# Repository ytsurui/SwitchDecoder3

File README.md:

# SwitchDecoder3

NMRA DCC規格のアクセサリパケットを受信して、直流二線式のポイント線路を動作させることができるアクセサリデコーダです。

本リポジトリには、基板設計データとファームウェア、動作確認用ファームウェアが含まれています。

## 開発環境

- KiCad 6.0.8
- Microchip Studio Version 7.0.2542

## 主要スペック

  * 組み立て後の基板サイズ: 15.5mm x 8.0mm
  * 推奨最大電圧: 16V
  * 出力電流: 最大2A (ピーク3A)
  * マイコン書き込み端子を用意し、実装後のプログラム書き換えも可能
    <br>UPDI 2pin Interface (GND / UPDI)

## 通常ファームウェア (Firmware)

設定したアクセサリアドレスに応じたDCCパケットを受信すると、ポイント線路を動作させます。

通電開始時にPROG端子に取り付けた配線をどちらかの線路に接触させることで、プログラムモードで起動します。

プログラムモードで起動している間に、同一のアクセサリアドレスに対する操作を連続して3回以上送信することで、設定されているアクセサリアドレスを送信したものに変更することができます。

また、CV値の書き込みにより、通電時間や通電開始までの遅延時間など、細かい動作の調整や、設定のリセットも可能です。

## 動作確認用ファームウェア (Firm_Test)

アクセサリアドレス「1」固定でDCCパケットを受信して動作できる機能と、PROG端子を線路に接触させると約1秒おきにポイント線路の転換動作を行うようにプログラムを作成してあります。

このファームウェアを書き込むことで、SwitchDecoder3基板のDCC入力、PROG端子、モータードライバ回路のすべてをテストすることができます。
  
## 各種ドキュメント

  * [マイコンのピンアサイン](docs/pin.md)
  * [パーツリスト](docs/partslist.md)
  * [CV値一覧](docs/cv_list.md)
  * [AVR Fuse Bitの設定内容](docs/avrfuse.md)

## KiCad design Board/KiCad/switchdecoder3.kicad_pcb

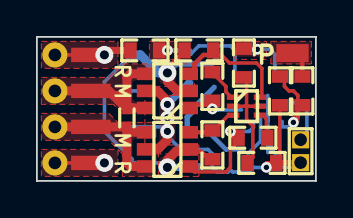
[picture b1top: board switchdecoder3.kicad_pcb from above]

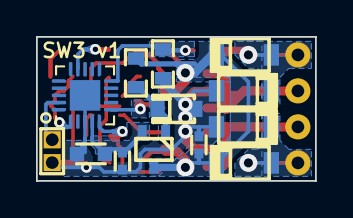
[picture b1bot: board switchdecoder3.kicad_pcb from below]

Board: 2 copper layers, 15.5 x 8.0 mm, 32 parts (13 on the bottom side), 20 nets.

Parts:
C1, C5: 104; C_1005
C3: 226; C_1608
C7: 182; C_1005
D1, D2, D3, D4: SS2040FL; PMDU
D5: UDZV5.1B; UMD2
P1, P2, P3, P4: PAD; PAD_2.2x0.8_SMD
P7: PROG; PAD_PROG_2PIN_HOLE0.7
P10: Test; Test_4pin_2mm
P11: PROG_PAD; PAD_1.0x1.8_SMD
Q1, Q2: DMG6601LVT; SOT-23-6
Q3: PMBT3904VS; SOT-666-nomark
Q5: 2SC4116; SC-70_v2
R1, R2, R17, R18: 104; R_1608
R3, R4, R7, R8: 102; R_1608
R5, R6: 331; R_1608
R12: 472; R_1608
U2: ATtiny406-M; VQFN-20-1EP_3x3mm_P0.4mm_EP1.7x1.7mm

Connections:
+5V: C3.1, C5.1, Q5.2 (E), U2.4 (VCC)
+12V: C1.1, D1.1 (K), D3.1 (K), Q1.2 (S), Q2.2 (S), Q5.3 (C), R3.1, R4.1, R12.1
/PROG: P11.1, R2.1
FWD: Q2.1 (G), R6.2, U2.5 (PA4)
GND: C1.2, C3.2, C5.2, D2.2 (A), D4.2 (A), D5.2 (A), P7.2, Q1.5 (S), Q2.5 (S), R8.2, R17.2, R18.2, U2.3 (GND), U2.21 (GND)
MOTOR+: C7.1, P3.1, P10.2, Q1.4 (D), Q1.6 (D)
MOTOR-: C7.2, P4.1, P10.3, Q2.4 (D), Q2.6 (D)
unnamed: D5.1 (K), Q5.1 (B), R12.2
unnamed: Q1.3 (G), Q3.6 (C1), R3.2
unnamed: Q2.3 (G), Q3.3 (C2), R4.2
unnamed: Q3.1 (E1), R5.1
unnamed: Q3.2 (B1), Q3.5 (B2), R7.2, R8.1
unnamed: Q3.4 (E2), R6.1
unnamed: R1.2, R17.1, U2.10 (PB4)
unnamed: R2.2, R18.1, U2.1 (PA2)
PWM: R7.1, U2.14 (PB0)
RAIL+: D1.2 (A), D2.1 (K), P1.1, P10.1, R1.1
RAIL-: D3.2 (A), D4.1 (K), P2.1, P10.4
REV: Q1.1 (G), R5.2, U2.6 (PA5)
UPDI: P7.1, U2.19 (~RESET/PA0)

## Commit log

2023-01-14 一部コマンドステーションでBiDiを有効にしている場合、パケットを認識しない問題を修正
2023-01-14 設定値読み出し中のDCCパケット受信に対応
2023-01-14 ポイント転換方向を修正
2023-01-14 バージョンコードを2に変更
2023-01-14 Service ModeのACK応答を調整
2024-03-21 receive cacheの処理を変更
2024-03-21 Lock Modeの設定を追加
2024-03-21 Lock Modeの動作を追加
2024-03-21 CVリスト: 自動ロックモード関連のCV説明を追加
2024-03-23 ロック時間と自動動作時間の分離
2024-03-23 通過時ロック・自動動作分離をCV一覧に反映
2025-12-30 LED表示を追加
2025-12-30 ドキュメントにLED関連を追加
2026-02-01 メモリ破壊バグを修正
2026-02-01 DCCバイトの判定時間を修正
2026-02-01 CV34の初期値を変更
